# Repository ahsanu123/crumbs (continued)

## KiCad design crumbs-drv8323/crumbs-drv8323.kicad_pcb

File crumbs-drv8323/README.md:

# Crumbs DRV8323

# Roadmap 

## References

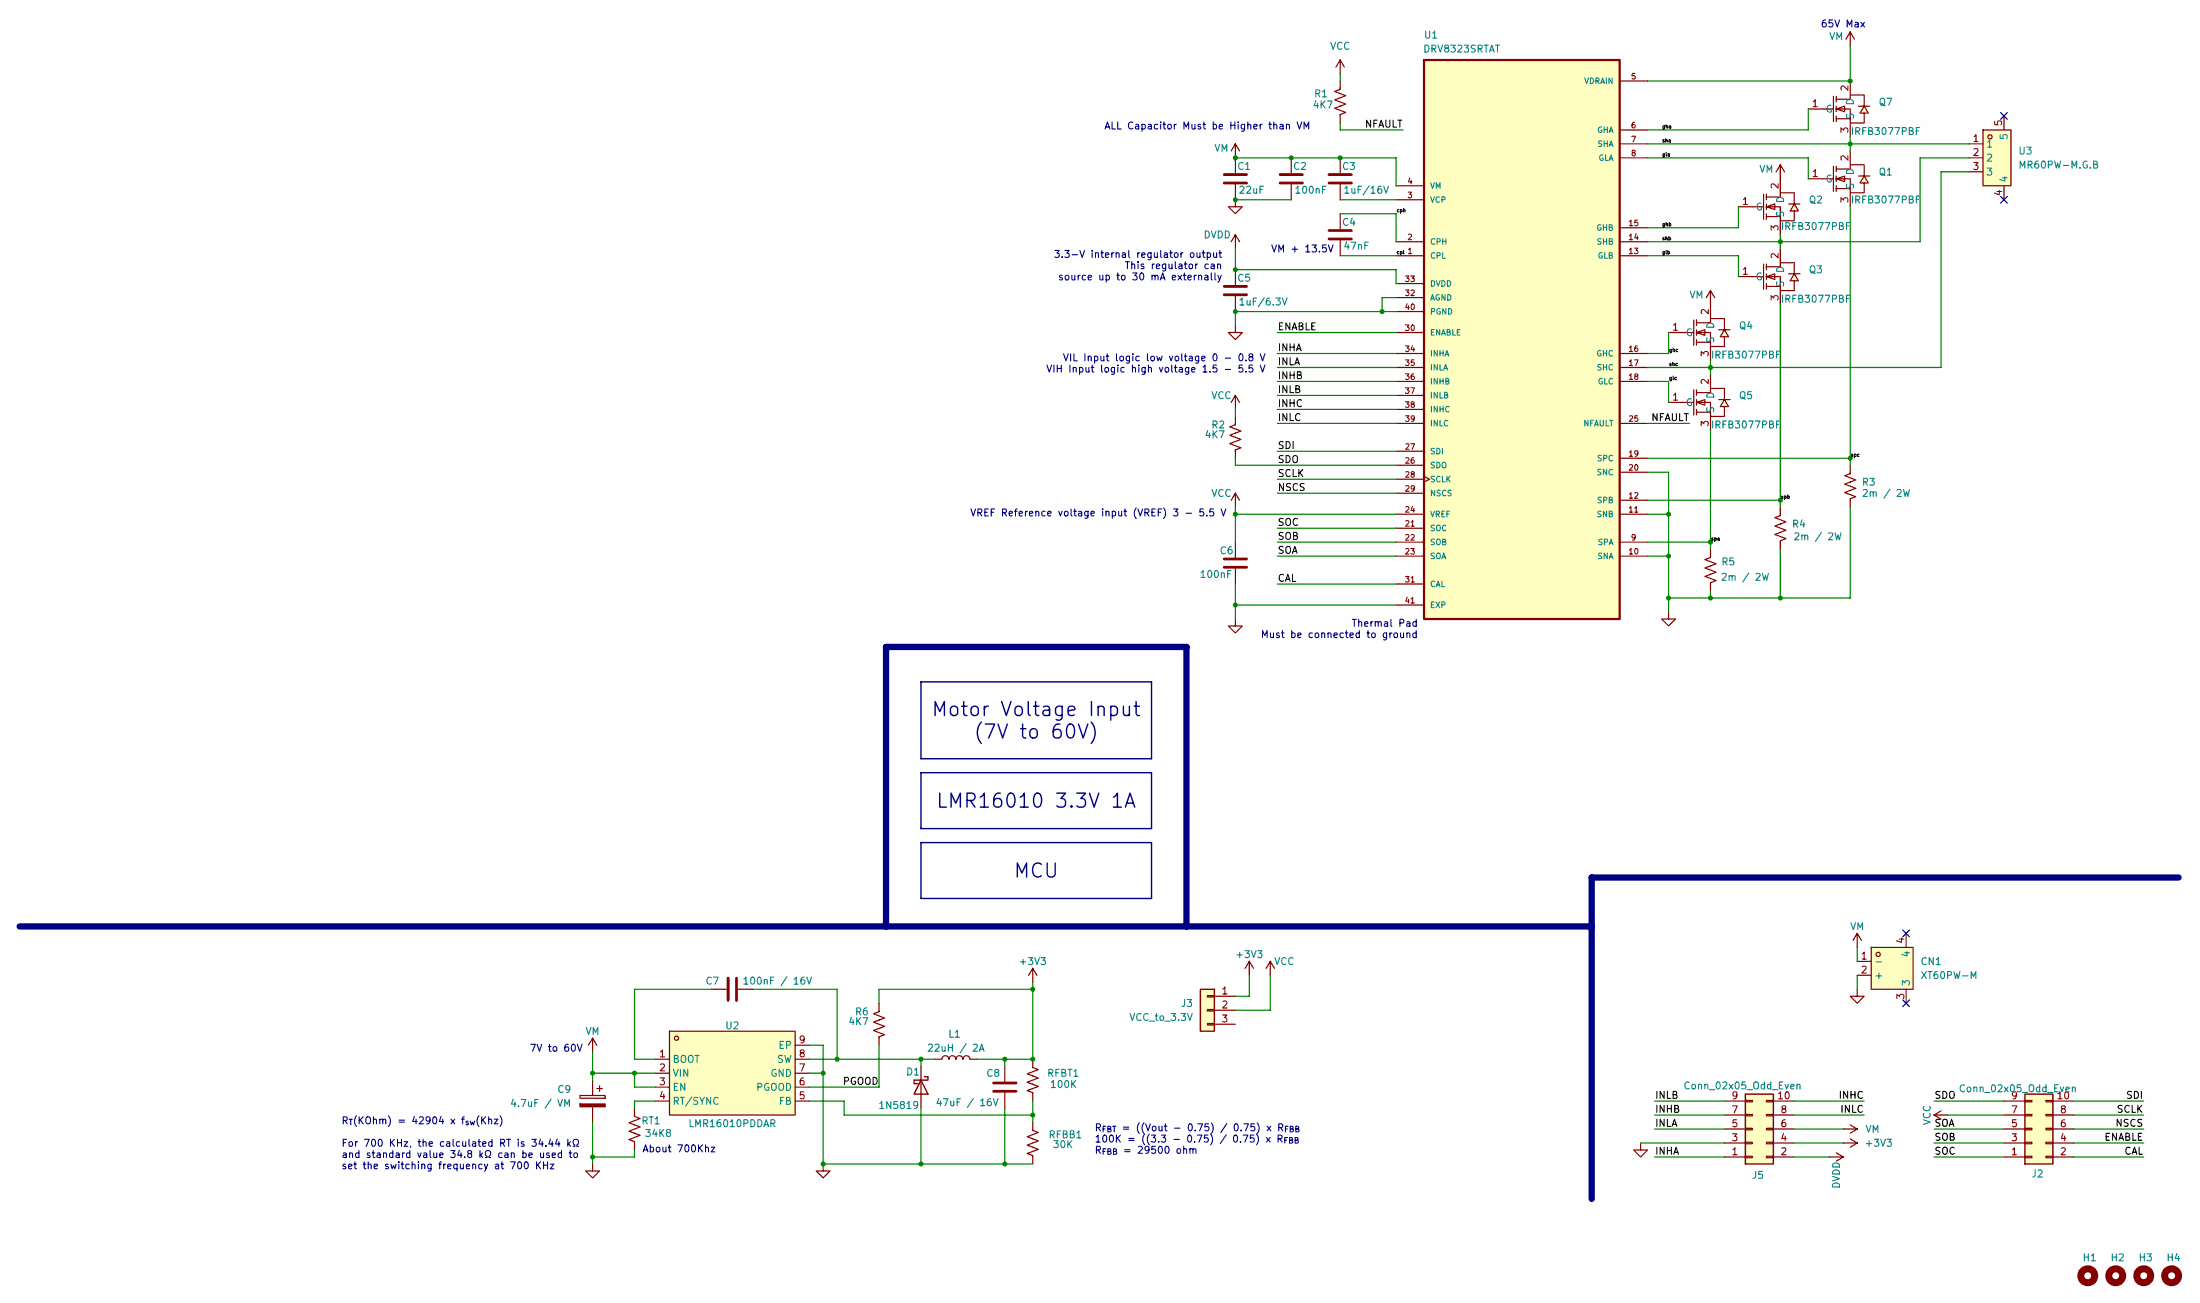
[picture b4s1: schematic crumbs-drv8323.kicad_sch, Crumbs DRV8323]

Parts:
C1: 22uF; C_Disc_D7.5mm_W5.0mm_P5.00mm
C2: 100nF; C_Disc_D7.5mm_W5.0mm_P5.00mm
C3: 1uF/16V; C_0805_2012Metric
C4: 47nF; C_Disc_D7.5mm_W5.0mm_P5.00mm
C5: 1uF/6.3V; C_0805_2012Metric
C6: 100nF; C_0805_2012Metric
C7: 100nF / 16V; C_0805_2012Metric
C8: 47uF / 16V; C_Disc_D7.5mm_W5.0mm_P5.00mm
C9: 4.7uF / VM; CP_Radial_D8.0mm_P2.50mm
CN1: XT60PW-M; CONN-TH_XT60PW-M; MPN XT60PW-M; LCSC Part C98732
D1: 1N5819; D_DO-41_SOD81_P10.16mm_Horizontal
H1, H2, H3, H4: MountingHole; MountingHole_2mm
J2, J5: Conn_02x05_Odd_Even; IDC-Header_2x05_P2.54mm_Vertical
J3: VCC_to_3.3V; PinHeader_1x03_P2.54mm_Vertical
L1: 22uH / 2A; L_1812_4532Metric
Q1, Q2, Q3, Q4, Q5, Q7: IRFB3077PBF; TO-220-3_Horizontal_TabDown; MPN IRFB3077PBF; LCSC Part C2641
R1, R2, R6: 4K7; R_0805_2012Metric
R3, R4, R5: 2m / 2W; R_2512_6332Metric
RFBB1: 30K; R_0805_2012Metric
RFBT1: 100K; R_0805_2012Metric
RT1: 34K8; R_0805_2012Metric
U1: DRV8323SRTAT; QFN50P600X600X80-41N415X415
U2: LMR16010PDDAR; SOPOWERPAD-8_L4.9-W3.9-P1.27-LS6.0-BL-EP; MPN LMR16010PDDAR; LCSC Part C183084
U3: MR60PW-M.G.B; CONN-TH_MR60PW; MPN MR60PW-M.G.B; LCSC Part C19268044

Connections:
+3V3: C8.2, J3.1, J5.4, L1.2, R6.1, RFBT1.1
/CAL: J2.2, U1.31 (CAL)
/ENABLE: J2.4, U1.30 (ENABLE)
/INHA: J5.1, U1.34 (INHA)
/INHB: J5.7, U1.36 (INHB)
/INHC: J5.10, U1.38 (INHC)
/INLA: J5.5, U1.35 (INLA)
/INLB: J5.9, U1.37 (INLB)
/INLC: J5.8, U1.39 (INLC)
/NFAULT: R1.2, U1.25 (NFAULT)
/NSCS: J2.6, U1.29 (NSCS)
/PGOOD: R6.2, U2.6 (PGOOD)
/SCLK: J2.8, U1.28 (SCLK)
/SDI: J2.10, U1.27 (SDI)
/SDO: J2.9, R2.2, U1.26 (SDO)
/SOA: J2.5, U1.23 (SOA)
/SOB: J2.3, U1.22 (SOB)
/SOC: J2.1, U1.21 (SOC)
/cph: C4.1, U1.2 (CPH)
/cpl: C4.2, U1.1 (CPL)
/gha: Q7.1 (G), U1.6 (GHA)
/ghb: Q2.1 (G), U1.15 (GHB)
/ghc: Q4.1 (G), U1.16 (GHC)
/gla: Q1.1 (G), U1.8 (GLA)
/glb: Q3.1 (G), U1.13 (GLB)
/glc: Q5.1 (G), U1.18 (GLC)
/sha: Q1.2 (D), Q7.3 (S), U1.7 (SHA), U3.1
/shb: Q2.3 (S), Q3.2 (D), U1.14 (SHB), U3.2
/shc: Q4.3 (S), Q5.2 (D), U1.17 (SHC), U3.3
/spa: Q5.3 (S), R5.1, U1.9 (SPA)
/spb: Q3.3 (S), R4.1, U1.12 (SPB)
/spc: Q1.3 (S), R3.1, U1.19 (SPC)
DVDD: C5.1, J5.2, U1.33 (DVDD)
GND: C1.2, C2.2, C5.2, C6.2, C8.1, C9.2, CN1.2 (+), D1.2 (A), J5.3, R3.2, R4.2, R5.2, RFBB1.2, RT1.2, U1.10 (SNA), U1.11 (SNB), U1.20 (SNC), U1.32 (AGND), U1.40 (PGND), U1.41 (EXP), U2.7 (GND), U2.9 (EP)
unnamed: C7.2, D1.1 (K), L1.1, U2.8 (SW)
unnamed: C3.2, U1.3 (VCP)
unnamed: C7.1, U2.1 (BOOT)
unnamed: RFBB1.1, RFBT1.2, U2.5 (FB)
unnamed: RT1.1, U2.4 (RT/SYNC)
VCC: C6.1, J2.7, J3.2, R1.1, R2.1, U1.24 (VREF)
VM: C1.1, C2.1, C3.1, C9.1, CN1.1 (-), J5.6, Q2.2 (D), Q4.2 (D), Q7.2 (D), U1.4 (VM), U1.5 (VDRAIN), U2.2 (VIN), U2.3 (EN)

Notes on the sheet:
3.3-V internal regulator output This regulator can source up to 30 mA externally
About 700Khz
VREF Reference voltage input (VREF) 3 - 5.5 V
R_{T}(KOhm) = 42904 x f_{sw}(Khz) For 700 KHz, the calculated RT is 34.44 kΩ and standard value 34.8 kΩ can be used to set the switching frequency at 700 KHz
VM + 13.5V
ALL Capacitor Must be Higher than VM
VIL Input logic low voltage 0 - 0.8 V VIH Input logic high voltage 1.5 - 5.5 V
7V to 60V
Thermal Pad Must be connected to ground
R_{FBT} = ((Vout - 0.75) / 0.75) x R_{FBB} 100K = ((3.3 - 0.75) / 0.75) x R_{FBB} R_{FBB} = 29500 ohm
65V Max
LMR16010 3.3V 1A
Motor Voltage Input (7V to 60V)
MCU

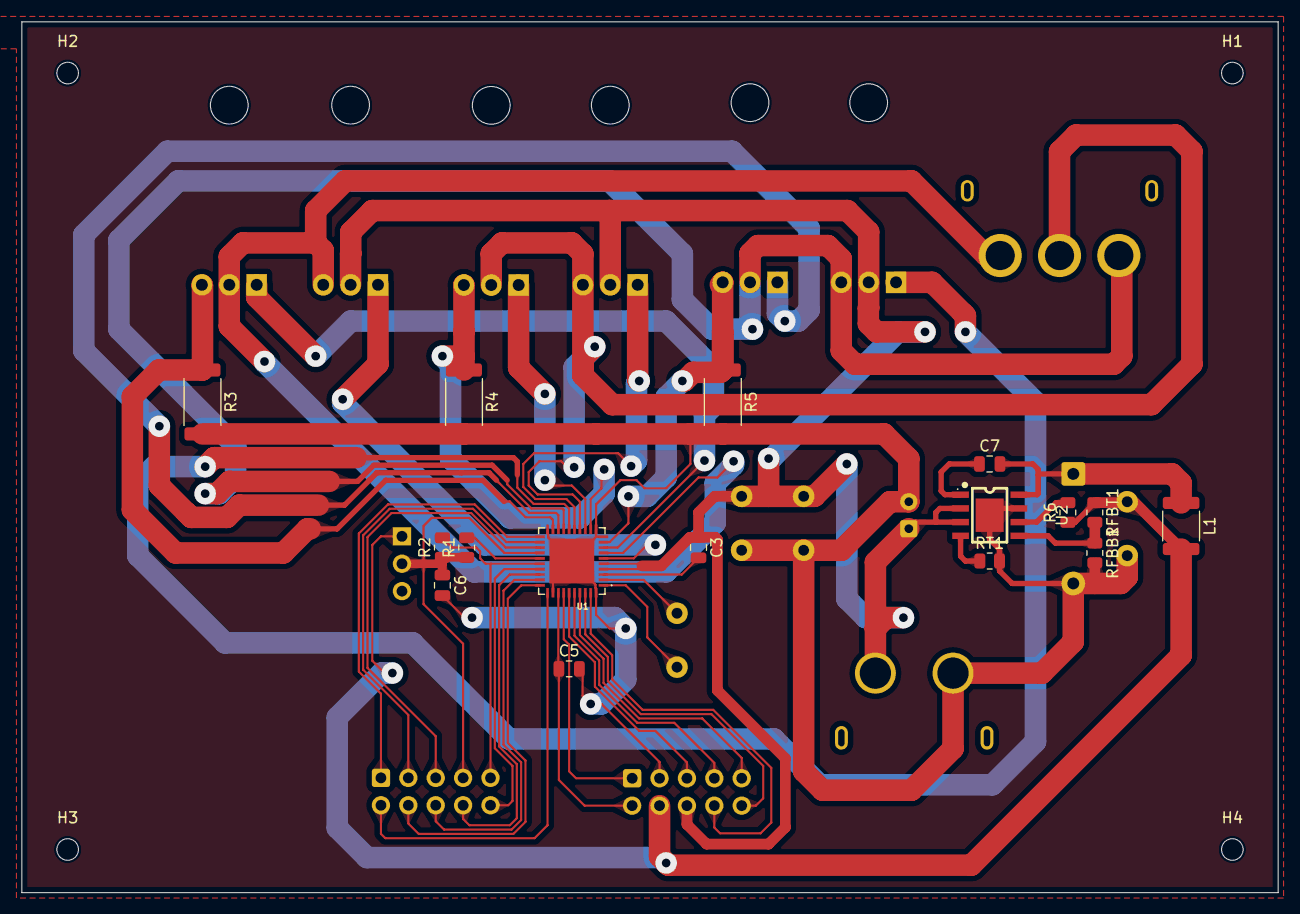
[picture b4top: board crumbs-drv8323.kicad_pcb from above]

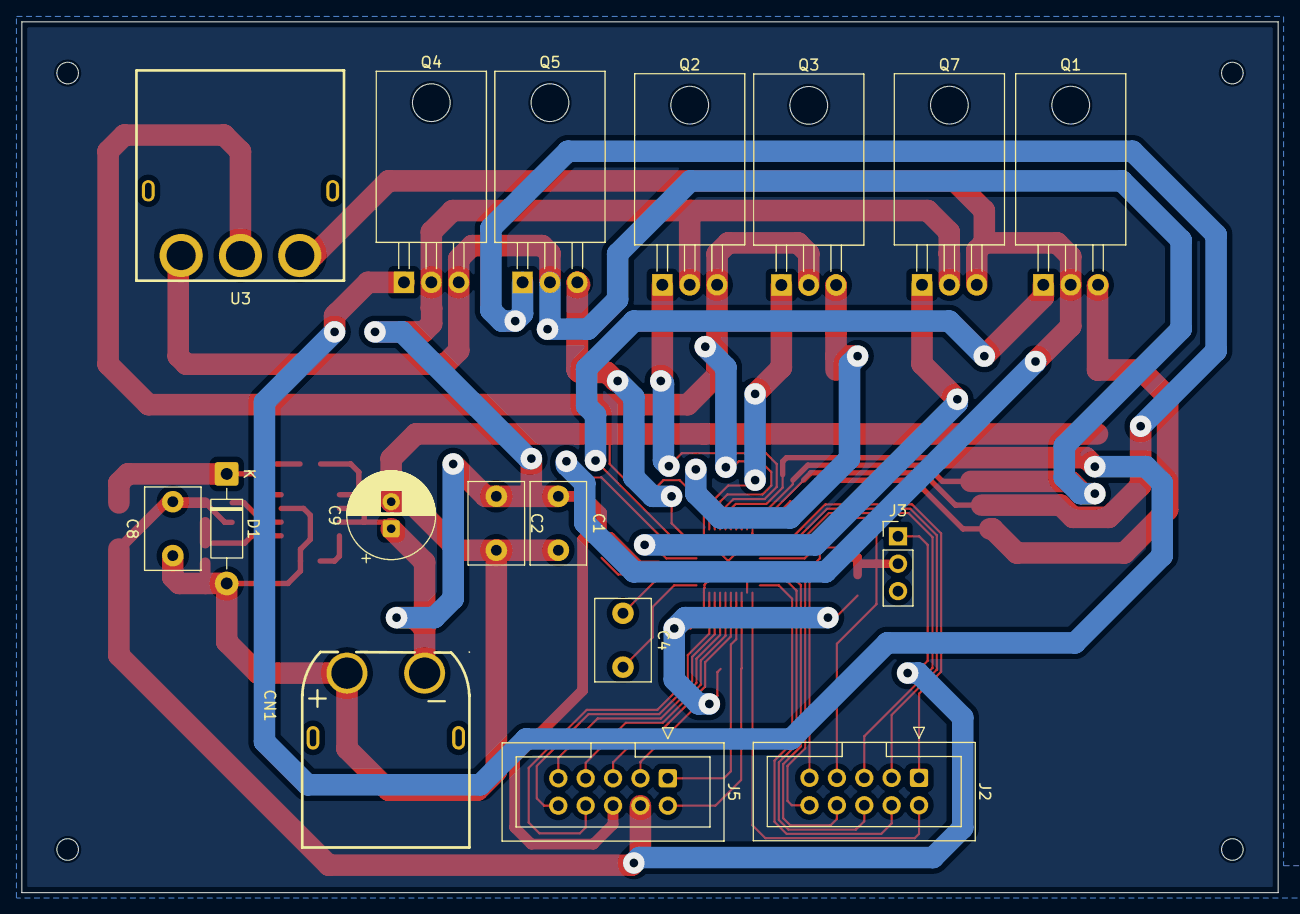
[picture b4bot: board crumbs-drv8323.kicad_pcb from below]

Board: 2 copper layers, 116.5 x 80.8 mm, 37 parts (17 on the bottom side), 41 nets.

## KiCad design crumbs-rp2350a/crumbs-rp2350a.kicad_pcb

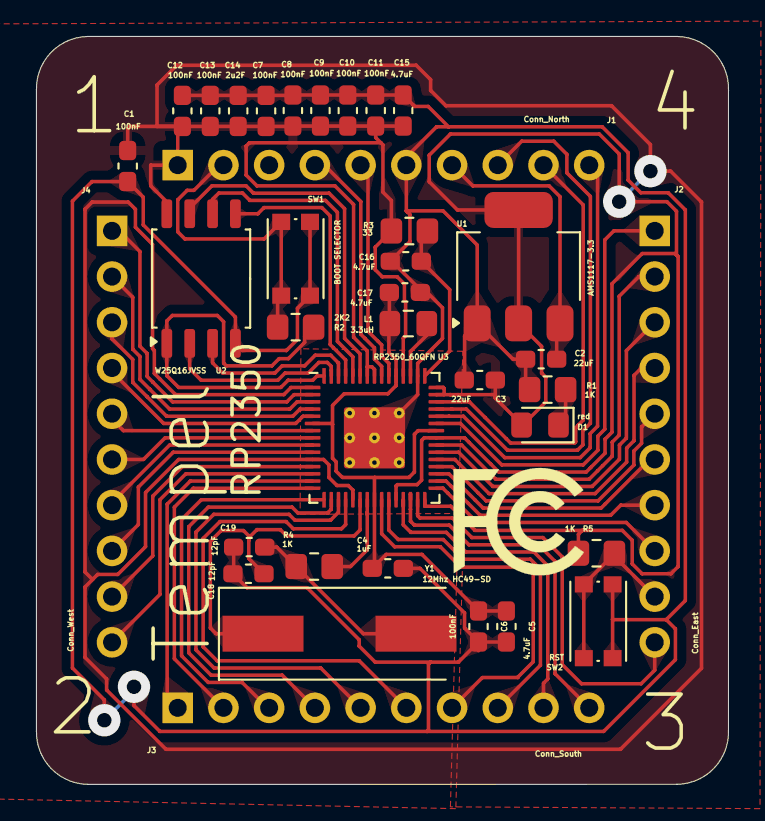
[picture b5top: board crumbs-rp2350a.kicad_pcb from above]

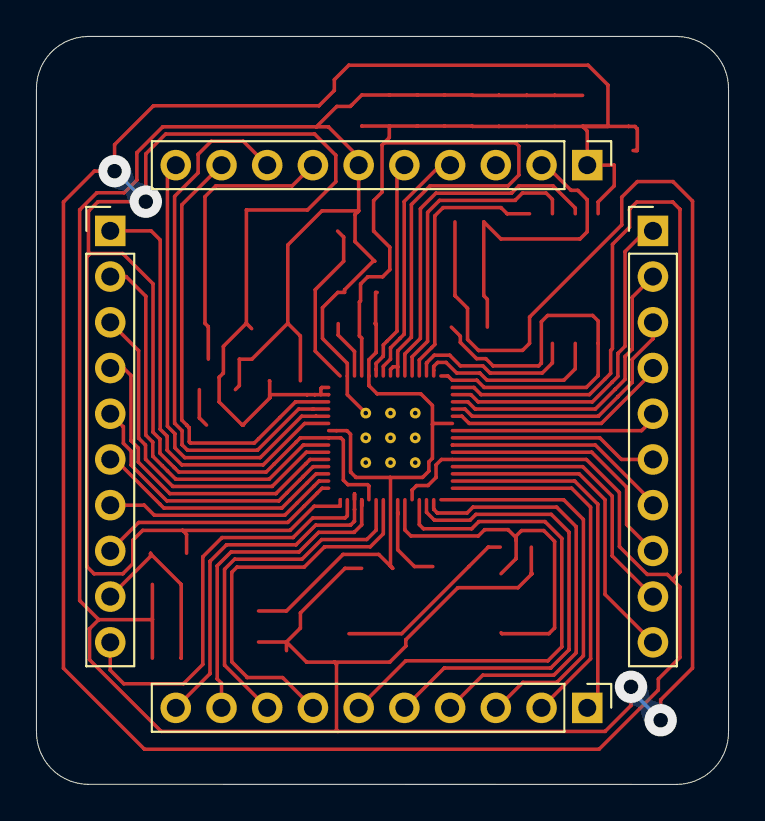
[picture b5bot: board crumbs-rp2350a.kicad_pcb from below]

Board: 2 copper layers, 38.4 x 41.6 mm, 36 parts (4 on the bottom side), 52 nets.

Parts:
C1, C6, C7, C8, C9, C10, C11, C12, C13: 100nF; C_0603_1608Metric_Pad1.08x0.95mm_HandSolder
C2, C3: 22uF; C_0603_1608Metric_Pad1.08x0.95mm_HandSolder
C4: 1uF; C_0603_1608Metric_Pad1.08x0.95mm_HandSolder
C5, C15, C16, C17: 4.7uF; C_0603_1608Metric_Pad1.08x0.95mm_HandSolder
C14: 2u2F; C_0603_1608Metric_Pad1.08x0.95mm_HandSolder
C18, C19: 12pF; C_0603_1608Metric_Pad1.08x0.95mm_HandSolder
D1: red; LED_0805_2012Metric_Pad1.15x1.40mm_HandSolder
J1: Conn_North; PinHeader_1x10_P2.54mm_Vertical
J2: Conn_East; PinHeader_1x10_P2.54mm_Vertical
J3: Conn_South; PinHeader_1x10_P2.54mm_Vertical
J4: Conn_West; PinHeader_1x10_P2.54mm_Vertical
L1: 3.3uH; L_0805_2012Metric_Pad1.15x1.40mm_HandSolder
R1, R4, R5: 1K; R_0805_2012Metric_Pad1.20x1.40mm_HandSolder
R2: 2K2; R_0805_2012Metric_Pad1.20x1.40mm_HandSolder
R3: 33; R_0805_2012Metric_Pad1.20x1.40mm_HandSolder
SW1: BOOT SELECTOR; SW_Push_1P1T_NO_CK_KMR2
SW2: RST; SW_Push_1P1T_NO_CK_KMR2
U1: AMS1117-3.3; SOT-223-3_TabPin2
U2: W25Q16JVSS; SOIC-8_5.23x5.23mm_P1.27mm
U3: RP2350_60QFN; RP2350-QFN-60-1EP_7x7_P0.4mm_EP3.4x3.4mm_ThermalVias
Y1: 12Mhz HC49-SD; Crystal_SMD_HC49-SD

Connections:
+1V1: C4.1, C5.1, C6.1, C17.1, L1.1, U3.6 (DVDD), U3.23 (DVDD), U3.39 (DVDD), U3.50 (VREG_FB)
+3.3V: C1.1, C3.1, C7.1, C8.1, C9.1, C10.1, C11.1, C12.1, C13.1, C14.1, C15.1, D1.2 (A), J1.1, R3.1, R5.2, U1.2 (VO), U2.8 (VCC), U3.1 (IOVDD), U3.11 (IOVDD), U3.20 (IOVDD), U3.26 (RUN), U3.30 (IOVDD), U3.38 (IOVDD), U3.44 (ADC_AVDD), U3.45 (IOVDD), U3.49 (VREG_VIN), U3.53 (USB_OTP_VDD), U3.54 (QSPI_IOVDD)
+5V: C2.1, J1.7, U1.3 (VI)
/GPIO0: J4.1, U3.2 (GPIO0)
/GPIO1: J4.2, U3.3 (GPIO1)
/GPIO2: J4.3, U3.4 (GPIO2)
/GPIO3: J4.4, U3.5 (GPIO3)
/GPIO4: J4.5, U3.7 (GPIO4)
/GPIO5: J4.6, U3.8 (GPIO5)
/GPIO6: J4.7, U3.9 (GPIO6)
/GPIO7: J4.8, U3.10 (GPIO7)
/GPIO8: J4.9, U3.12 (GPIO8)
/GPIO9: J4.10, U3.13 (GPIO9)
/GPIO10: J3.1, U3.14 (GPIO10)
/GPIO11: J3.2, U3.15 (GPIO11)
/GPIO12: J3.3, U3.16 (GPIO12)
/GPIO13: J3.4, U3.17 (GPIO13)
/GPIO14: J3.5, U3.18 (GPIO14)
/GPIO15: J3.6, U3.19 (GPIO15)
/GPIO16: J3.9, U3.27 (GPIO16)
/GPIO17: J3.10, U3.28 (GPIO17)
/GPIO18: J2.10, U3.29 (GPIO18)
/GPIO19: J2.8, U3.31 (GPIO19)
/GPIO20: J2.7, U3.32 (GPIO20)
/GPIO21: J2.6, U3.33 (GPIO21)
/GPIO22: J2.5, U3.34 (GPIO22)
/GPIO23: J2.4, U3.35 (GPIO23)
/GPIO24: J2.3, U3.36 (GPIO24)
/GPIO25: J2.2, U3.37 (GPIO25)
/GPIO26_ADC0: J2.1, U3.40 (GPIO26_ADC0)
/GPIO27_ADC1: J1.10, U3.41 (GPIO27_ADC1)
/GPIO28_ADC2: J1.8, U3.42 (GPIO28_ADC2)
/GPIO29_ADC3: J1.9, U3.43 (GPIO29_ADC3)
/SPI_SCLK: U2.6 (CLK), U3.56 (QSPI_SCLK)
/SPI_SD0: U2.5 (DI(IO0)), U3.57 (QSPI_SD0)
/SPI_SD1: U2.2 (DO(IO1)), U3.59 (QSPI_SD1)
/SPI_SD2: U2.3 (IO2), U3.58 (QSPI_SD2)
/SPI_SD3: U2.7 (IO3), U3.55 (QSPI_SD3)
/SPI_SS_N: R2.1, U2.1 (~CS), U3.60 (QSPI_SS)
/SWCLK: J3.7, U3.24 (SWCLK)
/SWD: J3.8, U3.25 (SWD)
/USB_DM: J1.5, U3.51 (USB_DM)
/USB_DP: J1.4, U3.52 (USB_DP)
/XIN: C18.1, U3.21 (XIN), Y1.1
/XOUT: R4.2, U3.22 (XOUT)
/~BOOTSEL: J1.2, R2.2, SW1.1
/~RST: J2.9, R5.1, SW2.1
GND: C1.2, C2.2, C3.2, C4.2, C5.2, C6.2, C7.2, C8.2, C9.2, C10.2, C11.2, C12.2, C13.2, C14.2, C15.2, C16.2, C17.2, C18.2, C19.2, J1.6, R1.2, SW1.2, SW2.2, U1.1 (GND), U2.4 (GND), U3.47 (VREG_PGND), U3.61 (GND)
unnamed: C19.1, R4.1, Y1.2
unnamed: D1.1 (K), R1.1
unnamed: C16.1, R3.2, U3.46 (VREG_AVDD)
unnamed: L1.2, U3.48 (VREG_LX)

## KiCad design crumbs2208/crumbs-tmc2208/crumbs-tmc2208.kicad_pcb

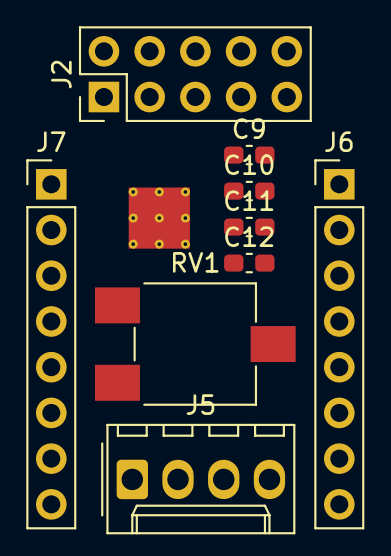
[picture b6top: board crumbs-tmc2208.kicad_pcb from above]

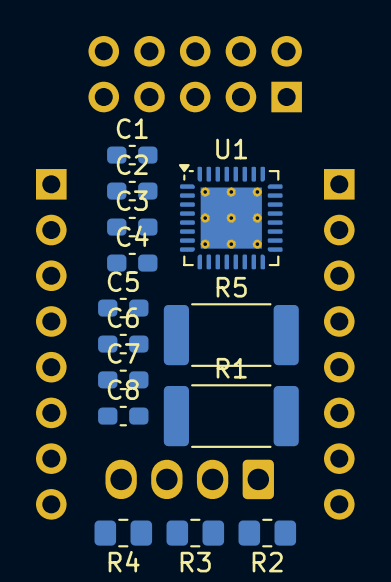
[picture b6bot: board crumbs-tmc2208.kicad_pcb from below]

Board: 2 copper layers, 23 parts (14 on the bottom side), 22 nets, no tracks yet.

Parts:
C1, C3, C4, C11, C12: 100nF/25V; C_0603_1608Metric_Pad1.08x0.95mm_HandSolder
C2: 100uF/25V; C_0603_1608Metric_Pad1.08x0.95mm_HandSolder
C5: 4.7uF/10V; C_0603_1608Metric_Pad1.08x0.95mm_HandSolder
C6: 22nF/50V; C_0603_1608Metric_Pad1.08x0.95mm_HandSolder
C7, C8, C9, C10: 470p/100V; C_0603_1608Metric_Pad1.08x0.95mm_HandSolder
J2: ENN/CLK/VREF/BRA/BRB; PinHeader_2x05_P2.54mm_Vertical
J5: MTR_OUT; Molex_KK-254_AE-6410-04A_1x04_P2.54mm_Vertical
J6: RIGHT; PinHeader_1x08_P2.54mm_Vertical
J7: LEFT; PinHeader_1x08_P2.54mm_Vertical
R1, R5: 150m/1W; R_2512_6332Metric_Pad1.40x3.35mm_HandSolder
R2: 10k; R_0805_2012Metric_Pad1.20x1.40mm_HandSolder
R3: 22k; R_0805_2012Metric_Pad1.20x1.40mm_HandSolder
R4: 20k; R_0805_2012Metric_Pad1.20x1.40mm_HandSolder
RV1: 20k; Potentiometer_ACP_CA6-VSMD_Vertical
U1: TMC2208-LA; TQFN-32-1EP_5x5mm_P0.5mm_EP3.4x3.4mm_ThermalVias

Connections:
+5V: C5.1, J2.1, J7.2, R2.1, R3.2, R4.1, U1.8 (5VOUT), U1.15 (VCC_IO)
/BRA: C11.1, J2.8, R1.1, U1.23 (BRA)
/BRB: C12.1, J2.10, R5.1, U1.27 (BRB)
/CLK: J2.4, J6.3, U1.13 (CLK)
/DIAG: J6.7, U1.11 (DIAG)
/DIR: J6.1, U1.19 (DIR)
/ENN: J2.2, J6.8, R2.2, U1.2 (ENN)
/INDEX: J7.7, U1.12 (INDEX)
/MS1: J6.5, U1.9 (MS1)
/MS2: J6.6, U1.10 (MS2)
/OA1: C7.1, J5.4, J7.3, U1.24 (OA1)
/OA2: C8.1, J5.3, J7.4, U1.21 (OA2)
/OB1: C9.1, J5.2, J7.5, U1.26 (OB1)
/OB2: C10.1, J5.1, J7.6, U1.1 (OB2)
/STEP: J6.2, U1.16 (STEP)
/UART: J6.4, R3.1, U1.14 (PDN_UART)
/VREF: J2.6, R4.2, RV1.3, U1.17 (VREF)
GND: C1.2, C2.2, C3.2, C5.2, C7.2, C8.2, C9.2, C10.2, C11.2, C12.2, J2.3, J2.5, J2.7, J2.9, J7.1, R1.2, R5.2, RV1.1, RV1.2, U1.3 (GND), U1.18 (GND)
unnamed: C6.2, U1.5 (CPI)
unnamed: C6.1, U1.4 (CPO)
unnamed: C4.2, U1.6 (VCP)
VBUS: C1.1, C2.1, C3.1, C4.1, J7.8, U1.22 (VS), U1.28 (VS)

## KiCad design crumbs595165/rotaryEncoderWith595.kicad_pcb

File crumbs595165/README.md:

## Crumbs 🍪 - Rotary Encoder With 74HC595 And 74HC165

Simple Breakout Board to Learn Shift Register with Tactile Switch And Rotary Encoder 

### 🍑 Features
> 🎈 4 Rotary Encoder With Low Pass Filter Debounce  
> 🏀 4 Input  With Low Pass Filter Debounce  
> 🍨 Use 2x 74HC595  
> 🍛 Use 2x 74HC165

<sup> 27 Juni 2024 19:11 Work In Progress, Made with ♥️ by AH... </sup>

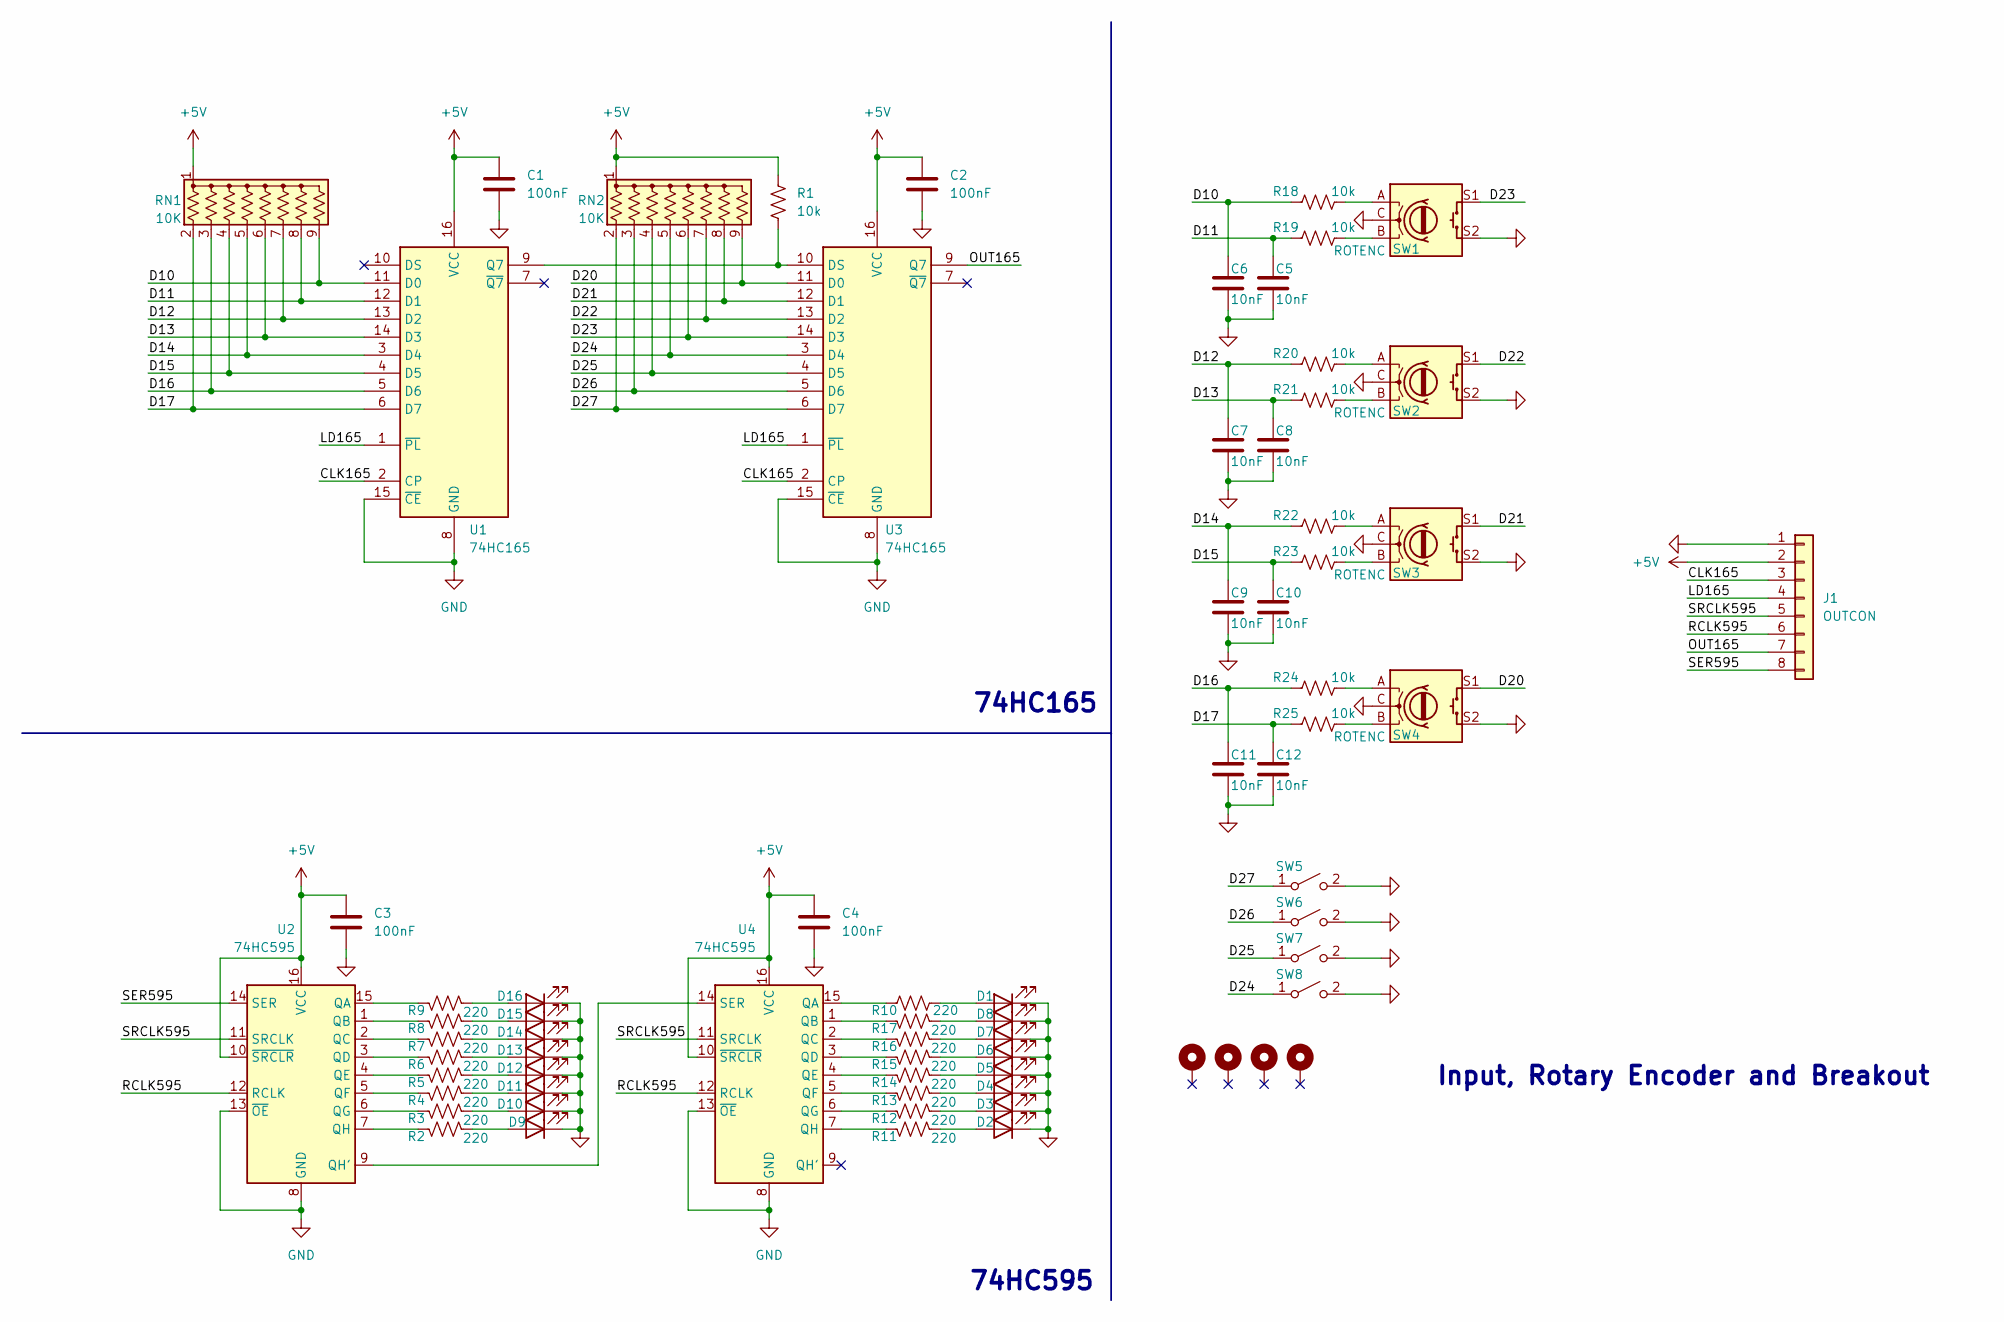
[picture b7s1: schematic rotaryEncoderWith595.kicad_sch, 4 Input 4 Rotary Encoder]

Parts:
C1, C2, C3, C4: 100nF; C_Rect_L4.0mm_W2.5mm_P2.50mm
C5, C6, C7, C8, C9, C10, C11, C12: 10nF; C_Rect_L4.0mm_W2.5mm_P2.50mm
D1, D2, D3, D4, D5, D6, D7, D8, D9, D10, D11, D12, D13, D14, D15, D16: LED; LED_D3.0mm
H1, H2, H3, H4: MountingHole_Pad; MountingHole_3mm_Pad
J1: OUTCON; PinSocket_1x08_P2.54mm_Vertical
R1, R18, R19, R20, R21, R22, R23, R24, R25: 10k; R_Axial_DIN0207_L6.3mm_D2.5mm_P10.16mm_Horizontal
R2, R3, R4, R5, R6, R7, R8, R9, R10, R11, R12, R13, R14, R15, R16, R17: 220; R_Axial_DIN0207_L6.3mm_D2.5mm_P10.16mm_Horizontal
RN1, RN2: 10K; R_Array_SIP9
SW1, SW2, SW3, SW4: ROTENC; RotaryEncoder_Alps_EC11E-Switch_Vertical_H20mm
SW5, SW6, SW7, SW8: IN; SW_PUSH_6mm
U1, U3: 74HC165; DIP-16_W7.62mm_LongPads
U2, U4: 74HC595; DIP-16_W7.62mm_LongPads

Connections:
+5V: C1.1, C2.1, C3.1, C4.1, J1.2, R1.1, RN1.1 (common), RN2.1 (common), U1.16 (VCC), U2.10 (~SRCLR), U2.16 (VCC), U3.16 (VCC), U4.10 (~SRCLR), U4.16 (VCC)
/CLK165: J1.3, U1.2 (CP), U3.2 (CP)
/D10: C6.1, R18.1, RN1.9 (R8), U1.11 (D0)
/D11: C5.1, R19.1, RN1.8 (R7), U1.12 (D1)
/D12: C7.1, R20.1, RN1.7 (R6), U1.13 (D2)
/D13: C8.1, R21.1, RN1.6 (R5), U1.14 (D3)
/D14: C9.1, R22.1, RN1.5 (R4), U1.3 (D4)
/D15: C10.1, R23.1, RN1.4 (R3), U1.4 (D5)
/D16: C11.1, R24.1, RN1.3 (R2), U1.5 (D6)
/D17: C12.1, R25.1, RN1.2 (R1), U1.6 (D7)
/D20: RN2.9 (R8), SW4.S1, U3.11 (D0)
/D21: RN2.8 (R7), SW3.S1, U3.12 (D1)
/D22: RN2.7 (R6), SW2.S1, U3.13 (D2)
/D23: RN2.6 (R5), SW1.S1, U3.14 (D3)
/D24: RN2.5 (R4), SW8.1 (A), U3.3 (D4)
/D25: RN2.4 (R3), SW7.1 (A), U3.4 (D5)
/D26: RN2.3 (R2), SW6.1 (A), U3.5 (D6)
/D27: RN2.2 (R1), SW5.1 (A), U3.6 (D7)
/LD165: J1.4, U1.1 (~PL), U3.1 (~PL)
/OUT165: J1.7, U3.9 (Q7)
/RCLK595: J1.6, U2.12 (RCLK), U4.12 (RCLK)
/SER595: J1.8, U2.14 (SER)
/SRCLK595: J1.5, U2.11 (SRCLK), U4.11 (SRCLK)
GND: C1.2, C2.2, C3.2, C4.2, C5.2, C6.2, C7.2, C8.2, C9.2, C10.2, C11.2, C12.2, D1.1 (K), D2.1 (K), D3.1 (K), D4.1 (K), D5.1 (K), D6.1 (K), D7.1 (K), D8.1 (K), D9.1 (K), D10.1 (K), D11.1 (K), D12.1 (K), D13.1 (K), D14.1 (K), D15.1 (K), D16.1 (K), J1.1, SW1.C, SW1.S2, SW2.C, SW2.S2, SW3.C, SW3.S2, SW4.C, SW4.S2, SW5.2 (B), SW6.2 (B), SW7.2 (B), SW8.2 (B), U1.8 (GND), U1.15 (~CE), U2.8 (GND), U2.13 (~OE), U3.8 (GND), U3.15 (~CE), U4.8 (GND), U4.13 (~OE)
unnamed: D1.2 (A), R10.2
unnamed: D2.2 (A), R11.2
unnamed: D3.2 (A), R12.2
unnamed: D4.2 (A), R13.2
unnamed: D5.2 (A), R14.2
unnamed: D6.2 (A), R15.2
unnamed: D7.2 (A), R16.2
unnamed: D8.2 (A), R17.2
unnamed: D9.2 (A), R2.2
unnamed: D10.2 (A), R3.2
unnamed: D11.2 (A), R4.2
unnamed: D12.2 (A), R5.2
unnamed: D13.2 (A), R6.2
unnamed: D14.2 (A), R7.2
unnamed: D15.2 (A), R8.2
unnamed: D16.2 (A), R9.2
unnamed: R18.2, SW1.A
unnamed: R19.2, SW1.B
unnamed: R20.2, SW2.A
unnamed: R21.2, SW2.B
unnamed: R22.2, SW3.A
unnamed: R23.2, SW3.B
unnamed: R24.2, SW4.A
unnamed: R25.2, SW4.B
unnamed: R1.2, U1.9 (Q7), U3.10 (DS)
unnamed: R9.1, U2.15 (QA)
unnamed: R8.1, U2.1 (QB)
unnamed: R7.1, U2.2 (QC)
unnamed: R6.1, U2.3 (QD)
unnamed: R5.1, U2.4 (QE)
unnamed: R4.1, U2.5 (QF)
unnamed: R3.1, U2.6 (QG)
unnamed: U2.9 (QH'), U4.14 (SER)
unnamed: R2.1, U2.7 (QH)
unnamed: R10.1, U4.15 (QA)
unnamed: R17.1, U4.1 (QB)
unnamed: R16.1, U4.2 (QC)
unnamed: R15.1, U4.3 (QD)
unnamed: R14.1, U4.4 (QE)
unnamed: R13.1, U4.5 (QF)
unnamed: R12.1, U4.6 (QG)
unnamed: R11.1, U4.7 (QH)

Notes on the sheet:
74HC165
74HC595
Input, Rotary Encoder and Breakout

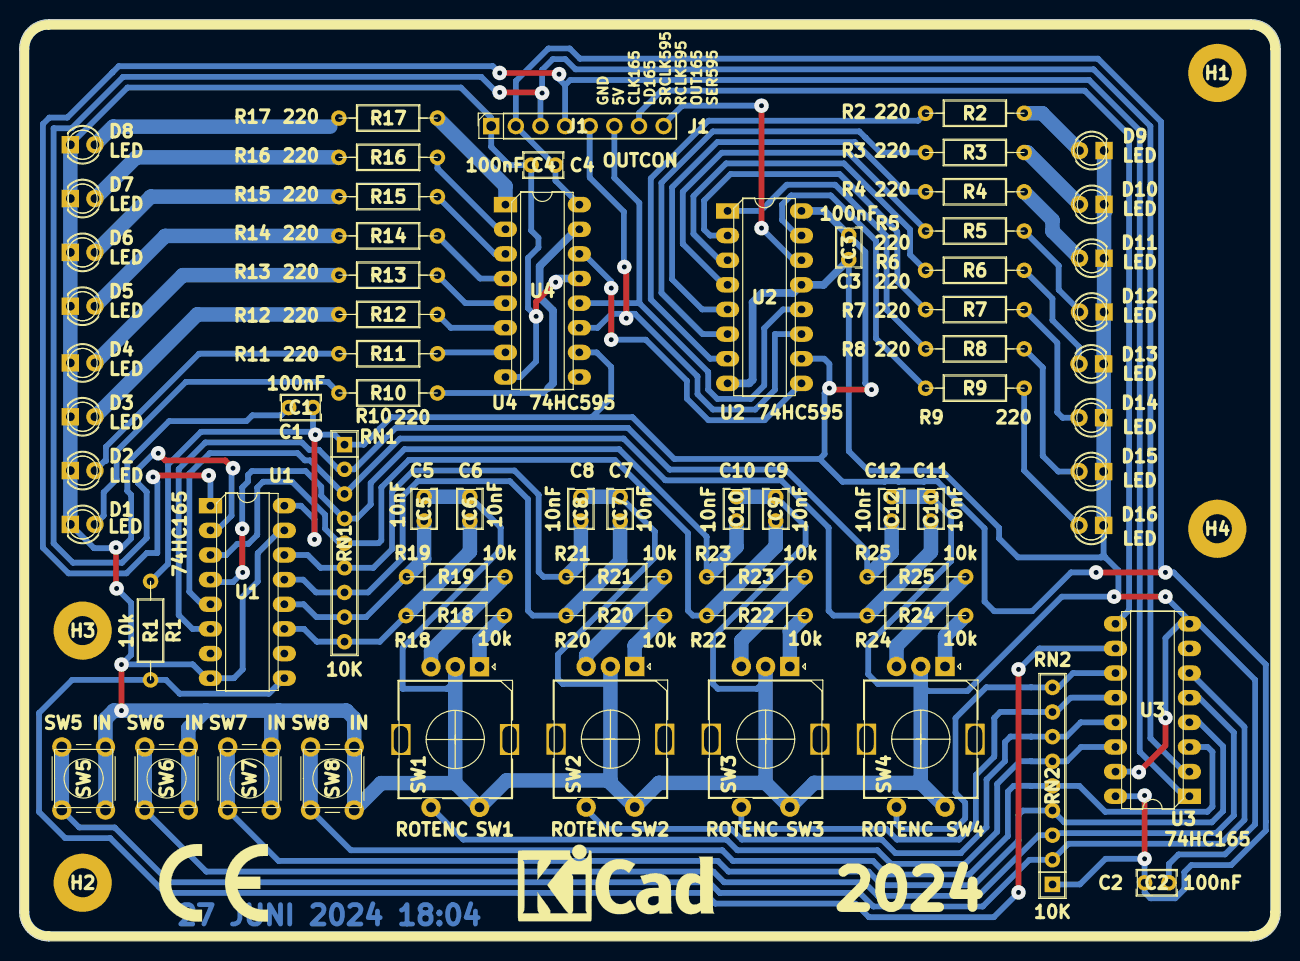
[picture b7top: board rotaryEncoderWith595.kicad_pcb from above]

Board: 2 copper layers, 130.0 x 95.0 mm, 72 parts (0 on the bottom side), 66 nets.
